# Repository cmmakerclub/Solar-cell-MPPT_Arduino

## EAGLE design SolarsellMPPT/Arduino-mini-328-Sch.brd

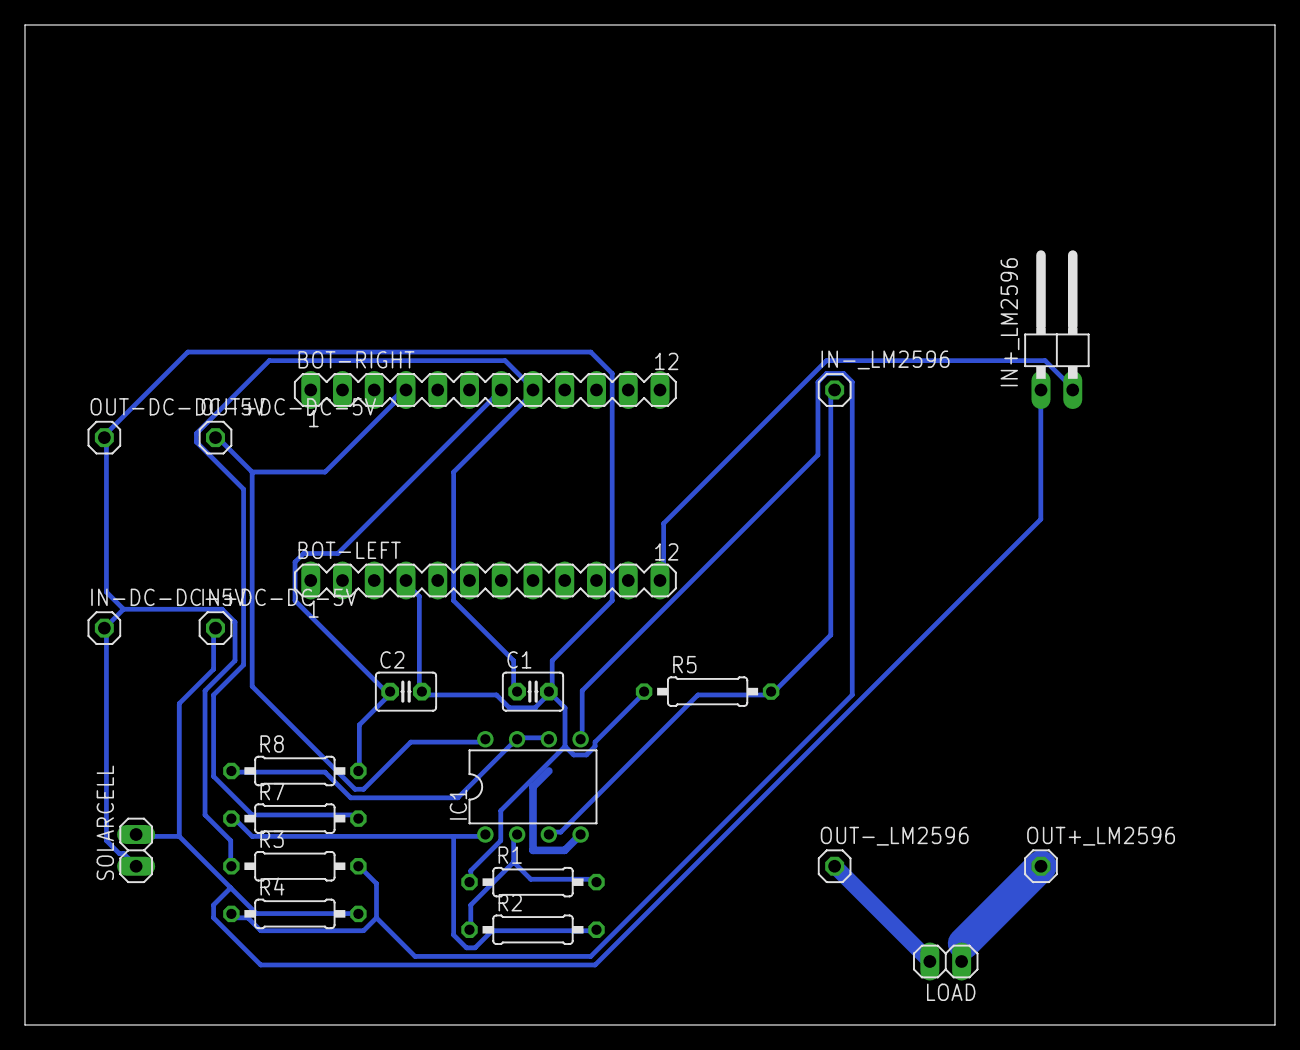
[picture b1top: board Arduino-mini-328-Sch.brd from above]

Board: 2 copper layers, 100.0 x 80.0 mm, 22 parts (0 on the bottom side), 12 nets.

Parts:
BOT-LEFT: MA12-1
BOT-RIGHT: MA12-1
C1, C2: 0.1uF; C025-030X050
IC1: LM358N; DIL08
IN+DC-DC-5V: 1X01
IN+_LM2596: 1X02/90
IN-DC-DC-5V: 1X01
IN-_LM2596: 1X01
LOAD: 1X02
OUT+DC-DC-5V: 1X01
OUT+_LM2596: 1X01
OUT-DC-DC-5V: 1X01
OUT-_LM2596: 1X01
R1: 1k; 0207/10
R2: 9k; 0207/10
R3: 237k; 0207/10
R4: 1M; 0207/10
R5: 0.1; 0207/10
R7, R8: 50; 0207/10
SOLARCELL: 1X02

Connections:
GNDA: BOT-LEFT.4, C1.2, C2.2, IN-DC-DC-5V.1, OUT-DC-DC-5V.1, R1.1, R3.1, R5.1, SOLARCELL.1
unnamed: IC1.1, R2.2, R7.1
unnamed: IC1.2, R1.2, R2.1
unnamed: BOT-LEFT.12, IN+_LM2596.2
unnamed: IC1.6, IC1.7, R8.1
unnamed: IC1.3, IN-_LM2596.1, R5.2
unnamed: BOT-RIGHT.8, C1.1, R7.2
unnamed: BOT-RIGHT.7, C2.1, R8.2
unnamed: IN+DC-DC-5V.1, IN+_LM2596.1, R4.2, SOLARCELL.2
unnamed: IC1.5, R3.2, R4.1
unnamed: LOAD.2, OUT-_LM2596.1
V+: BOT-RIGHT.4, IC1.8, OUT+DC-DC-5V.1

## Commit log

2014-12-17 Ver 1.00 non test
2014-12-18 Ver 1.1 test code ok,but no sun for test
2014-12-19 update data test and code
2014-12-19 code for ATtiny85
2014-12-25 Ver1.2 add new code and chaged PWM Fr
2014-12-26 chaged some code.
2014-12-27 update some code
2014-12-27 up pic วงจร
2014-12-30 อัพเดทบทความ
2015-01-05 อัพเดทบทความ เพิ่มโฟลวชาร์จการทำงาน จัดหน้า
2015-01-09 change for use LM2956
2015-01-09 PCB and Sch use IRL2203 to drive load
2015-01-09 update วงจรเขียนใน Engle
2015-01-09 fix some bug
2015-01-09 fix image
2015-01-09 fix image bug
2015-01-10 update Shc and PCB . use LM2596 to drive load
2015-01-10 chage some PCB
2015-03-27 chage some code
2015-06-11 Update new shc PBC
2015-06-11 up Jumper pic
2015-06-12 Fix PCB
2015-06-14 Update ผลการทดลอง รูป
